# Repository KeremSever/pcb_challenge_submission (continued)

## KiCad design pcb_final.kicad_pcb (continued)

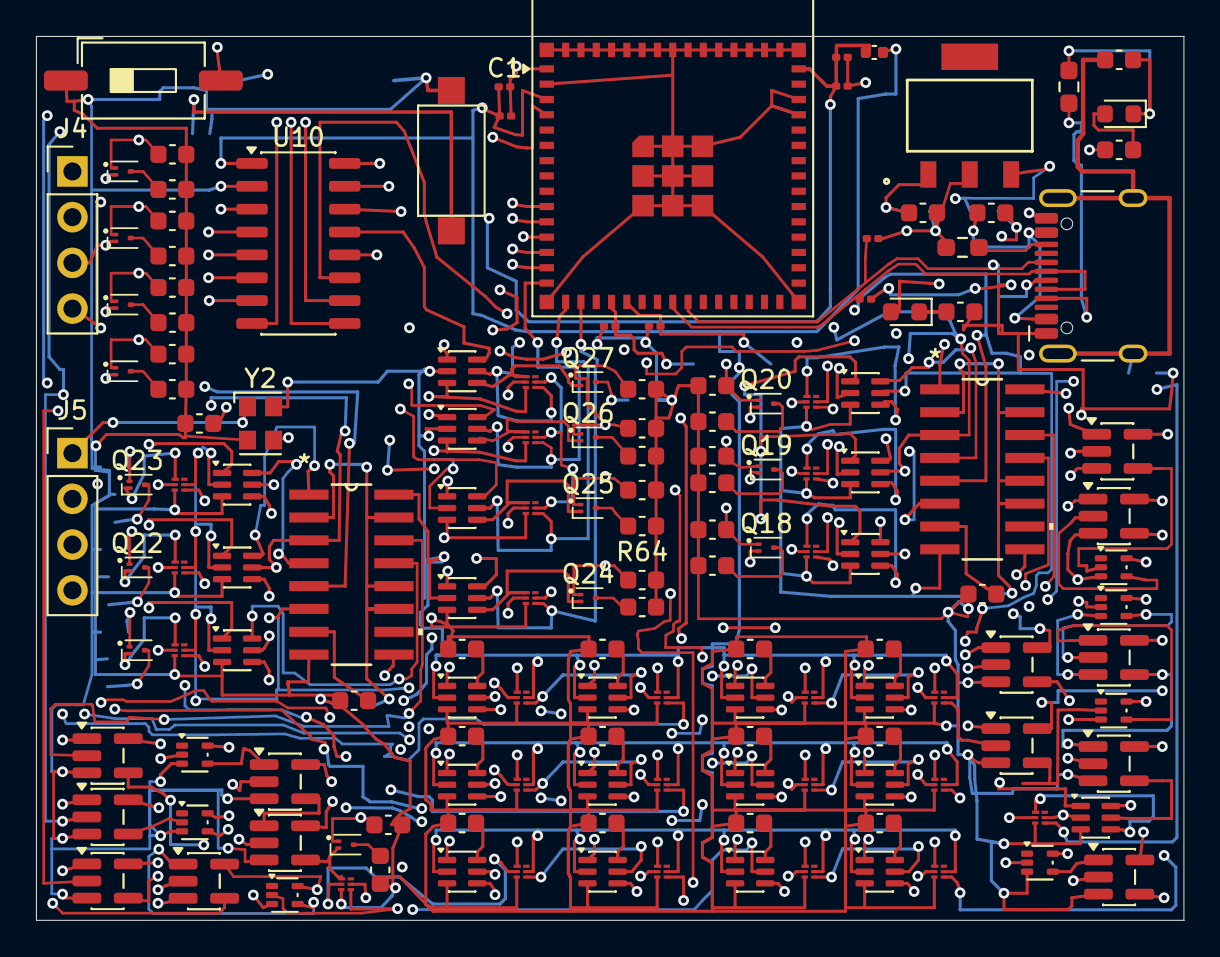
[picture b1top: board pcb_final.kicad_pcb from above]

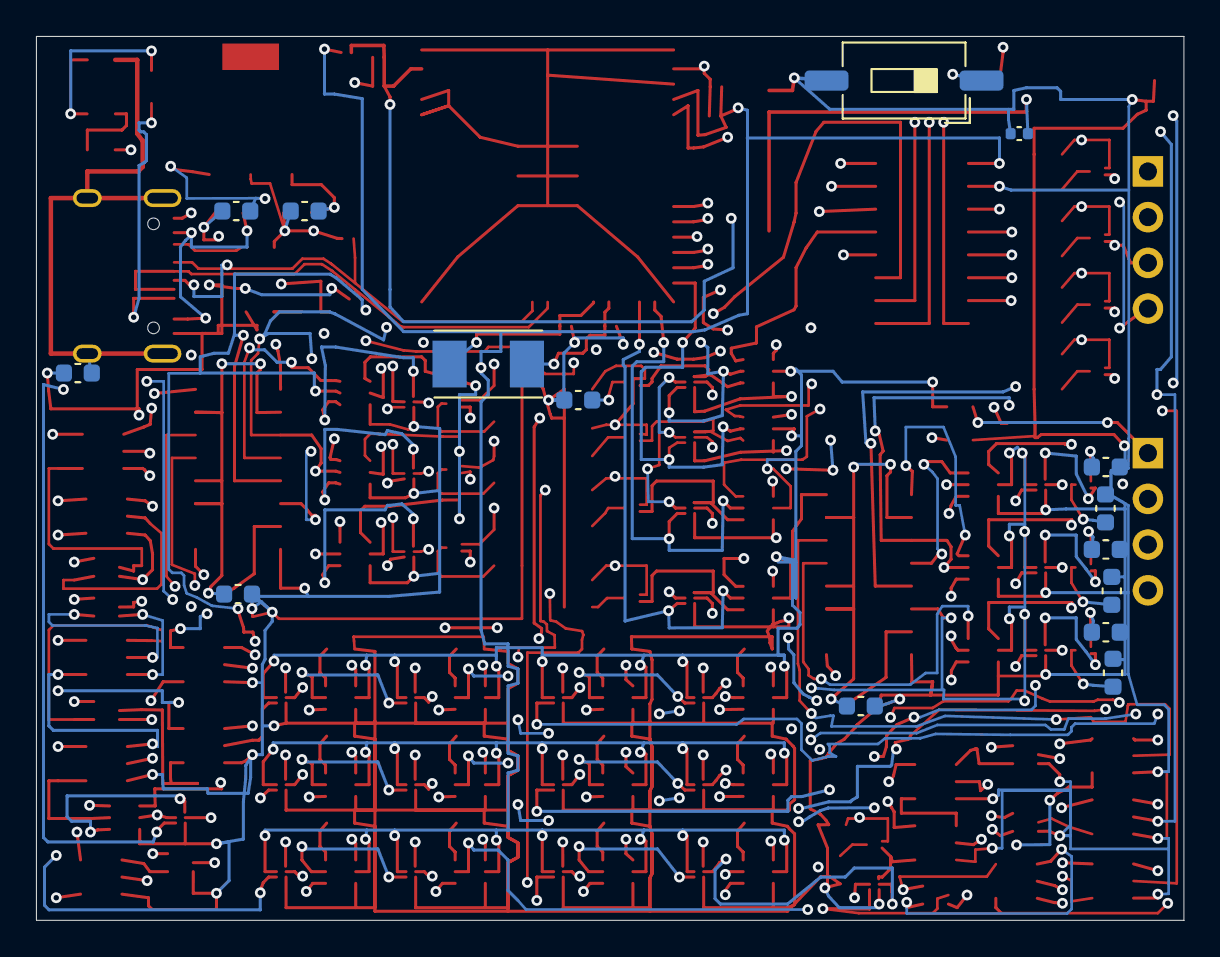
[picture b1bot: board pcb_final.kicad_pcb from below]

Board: 4 copper layers, 63.7 x 49.1 mm, 164 parts (15 on the bottom side), 135 nets.
